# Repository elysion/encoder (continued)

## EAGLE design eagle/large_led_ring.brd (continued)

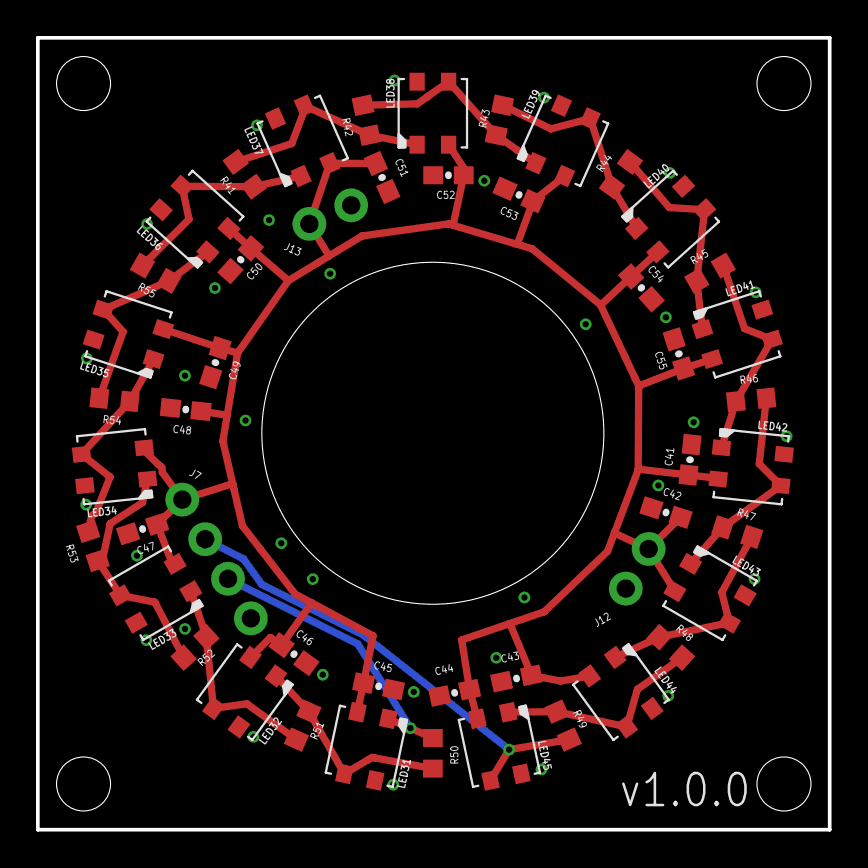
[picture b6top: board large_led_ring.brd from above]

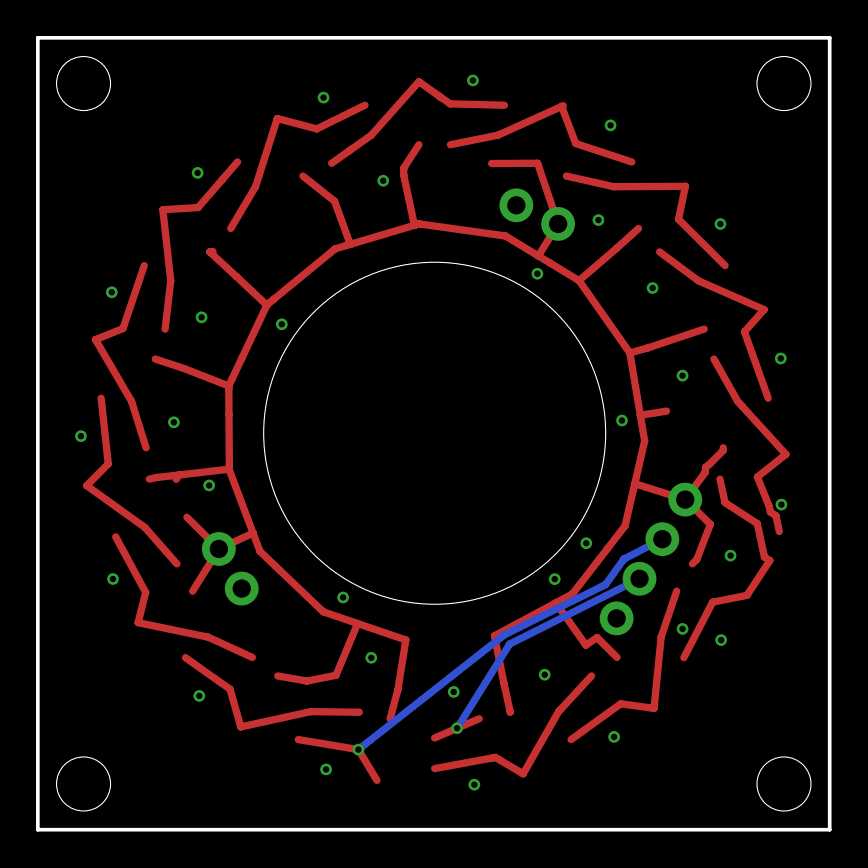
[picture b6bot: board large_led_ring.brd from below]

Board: 2 copper layers, 44.0 x 44.0 mm, 48 parts (3 on the bottom side), 18 nets.

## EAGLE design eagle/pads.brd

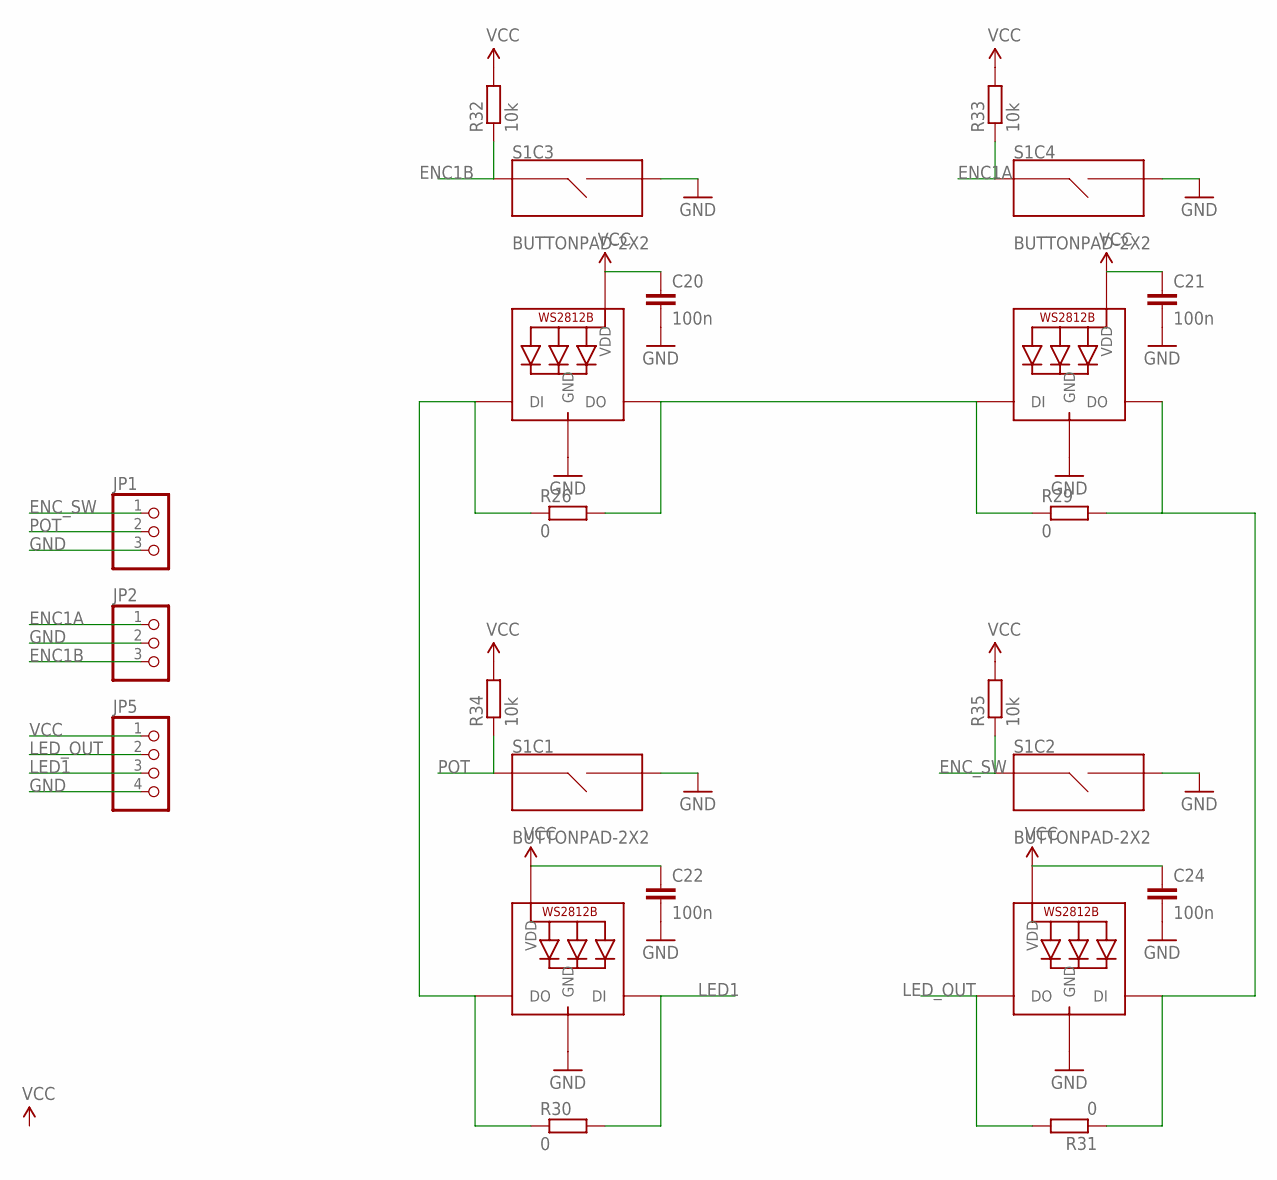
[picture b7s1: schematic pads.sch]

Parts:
C20, C21, C22, C24: 100n; 0603-CAP
JP1, JP2: PINHD-1X31X03_SMT; 1X03_SMT
JP5: PINHD-1X41X04_SMT; 1X04_SMT
LED16, LED17, LED18, LED19: WS2812B3535; LED3535
R26, R29, R30, R31: 0; R0603
R32, R33, R34, R35: 10k; R0603
S1: BUTTONPAD-2X2; BUTTONPAD-2X2-SINGLE

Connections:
ENC1A: JP2.1, R33.1, S1.SIG7 (SIG1)
ENC1B: JP2.3, R32.1, S1.SIG5 (SIG1)
ENC_SW: JP1.1, R35.1, S1.SIG3 (SIG1)
GND: C20.2, C21.2, C22.2, C24.2, JP1.3, JP2.2, JP5.4, LED16.4 (GND), LED17.4 (GND), LED18.4 (GND), LED19.4 (GND), S1.SIG2, S1.SIG4 (SIG2), S1.SIG6 (SIG2), S1.SIG8 (SIG2)
LED1: JP5.3, LED16.1 (DI), R30.2
LED_OUT: JP5.2, LED17.3 (DO), R31.2
unnamed: LED16.3 (DO), LED18.1 (DI), R26.1, R30.1
unnamed: LED17.1 (DI), LED19.3 (DO), R29.2, R31.1
unnamed: LED18.3 (DO), LED19.1 (DI), R26.2, R29.1
POT: JP1.2, R34.1, S1.SIG1
VCC: C20.1, C21.1, C22.1, C24.1, JP5.1, LED16.2 (VDD), LED17.2 (VDD), LED18.2 (VDD), LED19.2 (VDD), R32.2, R33.2, R34.2, R35.2

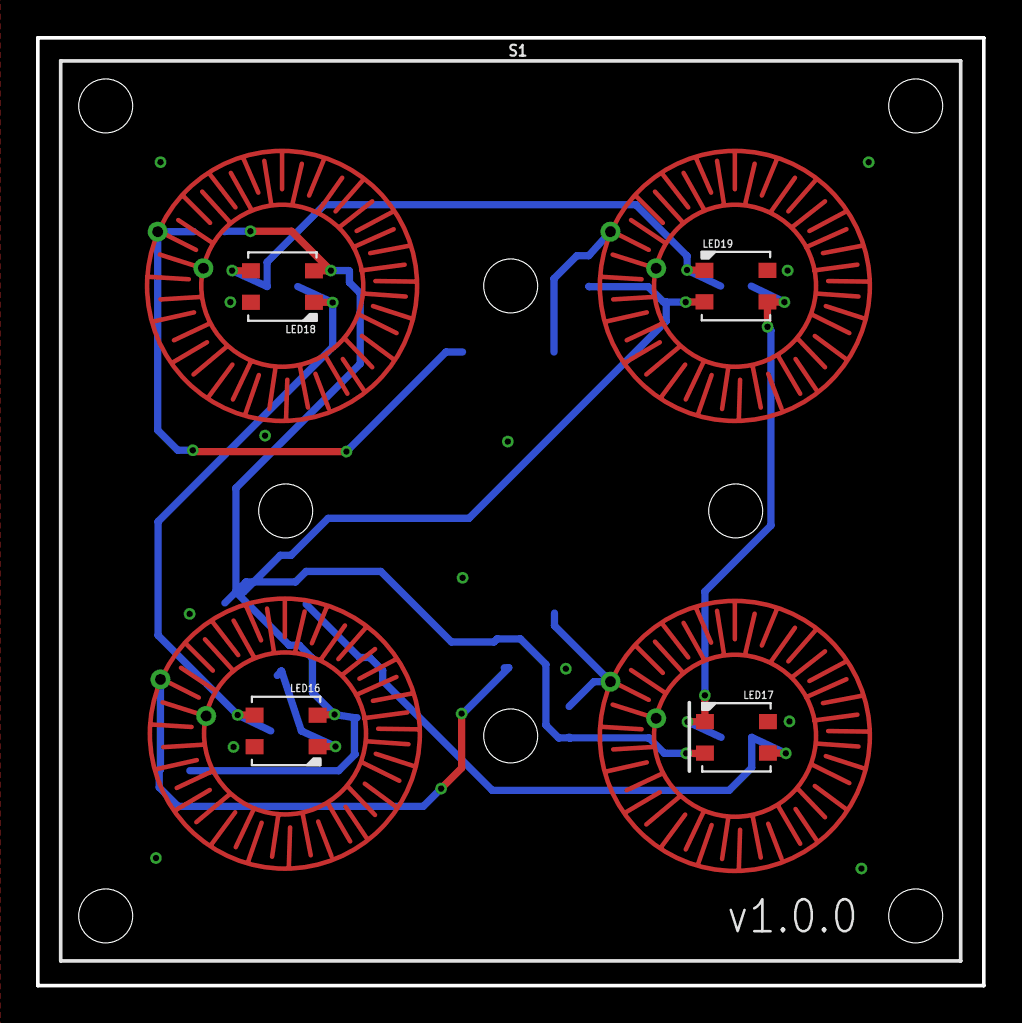
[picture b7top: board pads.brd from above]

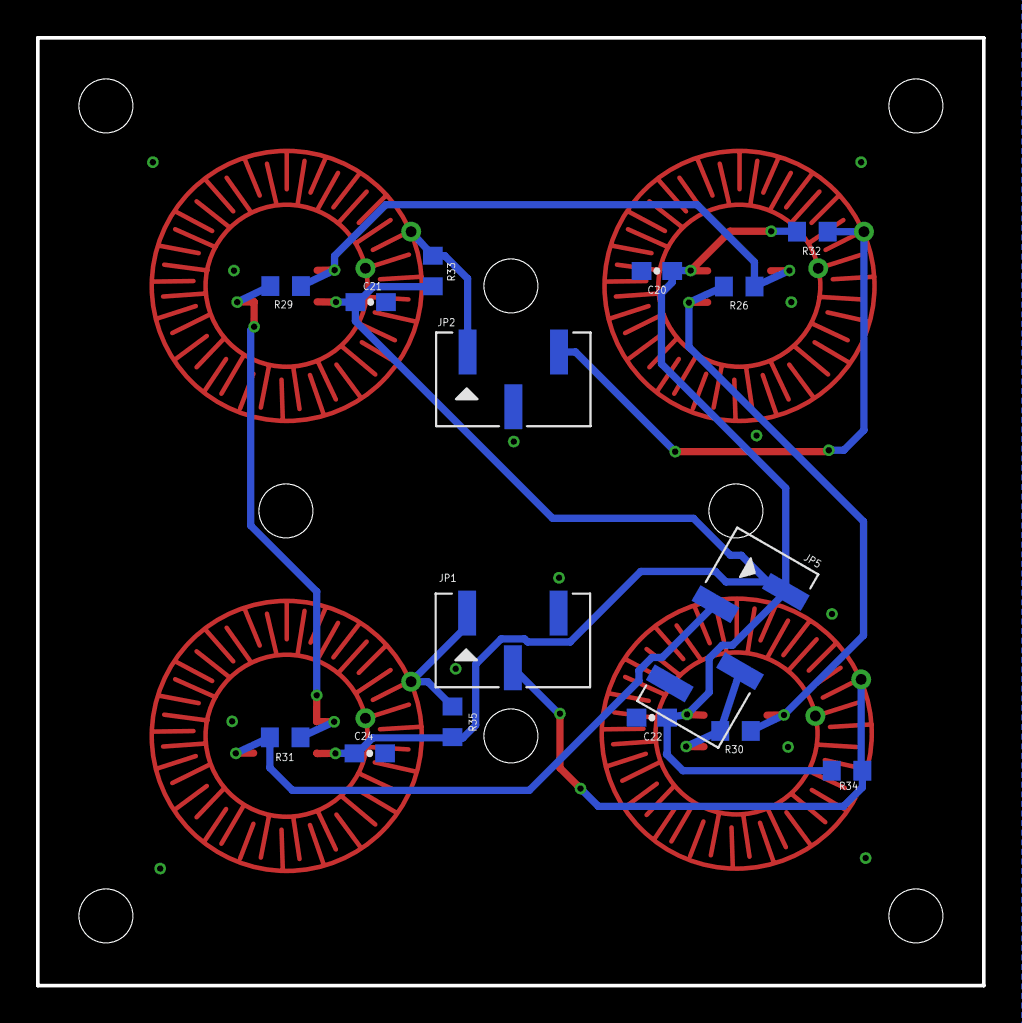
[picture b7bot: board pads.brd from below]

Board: 2 copper layers, 52.6 x 52.7 mm, 20 parts (15 on the bottom side), 11 nets.

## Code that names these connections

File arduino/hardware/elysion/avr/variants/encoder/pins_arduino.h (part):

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// ATMEL ATMEGA8 & 168 / ARDUINO
//
//                  +-\/-+
//            PC6  1|    |28  PC5 (AI 5)
//      (D 0) PD0  2|    |27  PC4 (AI 4)
//      (D 1) PD1  3|    |26  PC3 (AI 3)
//      (D 2) PD2  4|    |25  PC2 (AI 2)
// PWM+ (D 3) PD3  5|    |24  PC1 (AI 1)
//      (D 4) PD4  6|    |23  PC0 (AI 0)
//            VCC  7|    |22  GND
//            GND  8|    |21  AREF
//            PB6  9|    |20  AVCC
//            PB7 10|    |19  PB5 (D 13)
// PWM+ (D 5) PD5 11|    |18  PB4 (D 12)
// PWM+ (D 6) PD6 12|    |17  PB3 (D 11) PWM
//      (D 7) PD7 13|    |16  PB2 (D 10) PWM
//      (D 8) PB0 14|    |15  PB1 (D 9) PWM
//                  +----+
//
// (PWM+ indicates the additional PWM pins on the ATmega168.)
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
const uint8_t PROGMEM digital_pin_to_port_PGM[] = {
	NOT_A_PIN,
	PD, // PD3
	PD, // PD4
	NOT_A_PIN, // GND
	NOT_A_PIN, // VCC
	NOT_A_PIN, // GND
	NOT_A_PIN, // VCC
	PB, // PB6
	PB, // PB7
	PD, // PD5
	PD, // PD6
	PD, // PD7
	PB, // PB0
	PB, // PB1
	PB, // PB2
	PB, // PB3
	PB, // PB4
	PB, // PB5
	NOT_A_PIN, // VCC
	NOT_A_PIN, // ADC6
	NOT_A_PIN, // AREF
	NOT_A_PIN, // GND
	NOT_A_PIN, // ADC7
	PC, // PC0
	PC, // PC1
	PC, // PC2
	PC, // PC3
	PC, // PC4
	PC, // PC5
	PC, // PC6
	PD, // PD0
	PD, // PD1
	PD, // PD2
};

const uint8_t PROGMEM digital_pin_to_bit_mask_PGM[] = {
    0,
	_BV(3), // PD3
	_BV(4), // PD4
	0, // GND
	0, // VCC
	0, // GND
	0, // VCC
	_BV(6), // PB6
	_BV(7), // PB7
	_BV(5), // PD5
	_BV(6), // PD6
	_BV(7), // PD7
	_BV(0), // PB0
	_BV(1), // PB1
	_BV(2), // PB2
	_BV(3), // PB3
	_BV(4), // PB4
	_BV(5), // PB5
	0, // VCC
	0, // ADC6
	0, // AREF
	0, // GND
	0, // ADC7
	_BV(0), // PC0
	_BV(1), // PC1
	_BV(2), // PC2
	_BV(3), // PC3
	_BV(4), // PC4
	_BV(5), // PC5
	_BV(6), // PC6
	_BV(0), // PD0
	_BV(1), // PD1
	_BV(2), // PD2
};

const uint8_t PROGMEM digital_pin_to_timer_PGM[] = {
	NOT_ON_TIMER,
	TIMER2B, // PD3
	NOT_ON_TIMER, // PD4
	NOT_ON_TIMER, // GND
	NOT_ON_TIMER, // VCC
	NOT_ON_TIMER, // GND
	NOT_ON_TIMER, // VCC
	NOT_ON_TIMER, // PB6
	NOT_ON_TIMER, // PB7
	TIMER0B, // PD5
	TIMER0A, // PD6
	NOT_ON_TIMER, // PD7
	NOT_ON_TIMER, // PB0
	TIMER1A, // PB1
	TIMER1B, // PB2
	TIMER2A, // PB3
	NOT_ON_TIMER, // PB4
	NOT_ON_TIMER, // PB5
	NOT_ON_TIMER, // VCC
	NOT_ON_TIMER, // ADC6
	NOT_ON_TIMER, // AREF
	NOT_ON_TIMER, // GND
	NOT_ON_TIMER, // ADC7
	NOT_ON_TIMER, // PC0
	NOT_ON_TIMER, // PC1
	NOT_ON_TIMER, // PC2
	NOT_ON_TIMER, // PC3
	NOT_ON_TIMER, // PC4
	NOT_ON_TIMER, // PC5
	NOT_ON_TIMER, // PC6
	NOT_ON_TIMER, // PD0
	NOT_ON_TIMER, // PD1
	NOT_ON_TIMER, // PD2
};

#endif /* ARDUINO_MAIN */
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// TODO: Update for new version / create a new header / define a version macro
#if PCB_VERSION == 1
// L2 MSK1
#define ENCL2A (25)
#define ENCL2B (26)
// L1 MSK2
#define ENCL1A (2)
#define ENCL1B (32)
// M MSK2
#define ENC1A (31)
#define ENC1B (30)
// R1 MSK0
#define ENCR1A (8)
#define ENCR1B (7)
// R2 MSK1 & MSK0
#define ENCR2A (23)
#define ENCR2B (13)

// MSK2
#define SWL (1)
#define SWM (11)
#define SWR (9)
#define SWITCH_PORT (PIND)
#elif PCB_VERSION == 2 // TODO: these correspond to pins in i2c_encoder_4.*
#define ENC1A (30)
#define ENC1B (26)

// TODO: check the values below
#define ENCL1A (1)
#define ENCL1B (2)
#define ENCL2A (32)
#define ENCL2B (31)
#define ENCR1A (7)
#define ENCR1B (8)
#define ENCR2A (12)
#define ENCR2B (13)
#define SWM (23)
#define SWL (24)
#define SWR (25)
#define SWITCH_PORT (PINC)
#elif PCB_VERSION == 3
#define ENCM1A (9)
#define ENCM1B (10)
#define ENCM2A (12)
#define ENCM2B (13)
#define ENCL1A (23)
#define ENCL1B (24)
#define ENCL2A (31)
#define ENCL2B (30)
#define ENCR1A (2)
#define ENCR1B (1)
#define ENCR2A (7)
#define ENCR2B (8)
#define SWM (19)
#define SWL (22)
#define SWR (26)
#endif

#define TOUCH (11)

#if PCB_VERSION == 3
#define LEDL (25)
#define LEDM (11)
#define LEDR (32)
#else
#if PCB_VERSION == 1
#define LED1 (24)
#elif PCB_VERSION == 2
#define LED1 (9)
#endif
#define LED2 (10)
#endif

#if PCB_VERSION != 3
// TODO: On v2 SWM is connected to TOUCH -> Not an analog input
#define POTM SWM
#define POTL SWL
#define POTR SWR
#endif

#define NOT_POSSIBLE (-1)
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#endif

#if PCB_VERSION == 3 // TODO: add interrupt mask validation (i.e. != -1)
static const uint8_t SW_INTS_MASK = (1 << digitalPinToPCMSKbit(SWM));
#else
static const uint8_t SW_INTS_MASK = (1 << digitalPinToPCMSKbit(SWL)) | (1 << digitalPinToPCMSKbit(SWM)) | (1 << digitalPinToPCMSKbit(SWR));
#endif

#if PCB_VERSION == 3
static const uint8_t SW_INTS[] = {(byte) NOT_POSSIBLE, (byte) NOT_POSSIBLE, digitalPinToPCMSKbit(SWM), (byte) NOT_POSSIBLE};
#else
static const uint8_t SW_INTS[] = {(byte) NOT_POSSIBLE, digitalPinToPCMSKbit(SWL), digitalPinToPCMSKbit(SWM), digitalPinToPCMSKbit(SWR)};
#endif
/*
static const uint8_t TOUCH_INTS[] = {(byte) NOT_POSSIBLE, SWL_INT, PCINT23, SWR_INT};
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
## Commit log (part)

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2019-04-01 Add custom Arduino board
2019-04-01 Add Eagle design files
2019-04-14 Modularize WIP
2019-04-23 TEMP
2019-09-17 Add version text to boards;
    Make the text locked in order to make replacing it with e.g. sed easier
2019-09-17 TEMP: encoders working with weird delay, buttons not workin
2019-09-17 Add utility for updating board versions
2019-10-11 Move Arduino hardware files under arduino folder
2019-10-11 Make constants explicitly static
2019-10-11 Move configuration to config.h
2019-10-11 Rename SW1 to SWM and POT1 to POTM;
    Requires an updated pins_arduino.h
2019-10-11 Re-introduce encoder types;
    Was somehow removed at some point :shrug:
2019-10-12 Add Eagle temp files to ignore
2019-10-12 Toggle built-in led on boot and when sending messages
2019-10-12 Remove unnecessary comment
2019-10-12 Add feature validation into VCS;
    Somehow it was not added before.
2019-10-12 Add panelization command generator sheet
2019-10-13 Initialize PCINTs with enablePCINT
2019-10-13 Blink slave led to know it is alive and well
2019-10-13 Separate I2C and interrupt setup to functions
2019-10-13 Better indent for #define
2019-10-13 Remove warnings when compiling
2019-10-13 Comment out potentiometer code from v3
2019-10-13 Add warnings to prevent accidential freezes on ISRs
2019-10-13 FIX: update ANY_BOARD_HAS_FEATURE to include M1 and M2 for v3;
    Why does this not fail when using the old version with the newer PCB?
    BOARD_FEATURES_M should not be defined!
2019-10-13 Add parenthesis to fix switch state reading logic
2019-10-20 WIP multiple button support
2019-10-20 Add FFC connector interface versions to boards;
    It would be nice to keep the versions such that minor updates are
    backward compatible i.e. older encoder boards work with newer connector
    boards if the IF version difference is only a minor one.
2019-10-20 Add pogoprog pads on both sides of board
2019-10-20 Update switch voltage divider and connect encoder touch to it
2019-10-20 Make room for v-score on the edges by rotating connectors 45degs
2019-10-20 Board version 4 WIP;
    * Added solder pads to FFC connectors
    * Fixed naming of connectors (previously M was on the right and labels
    were wrong
    * Flipped builtin led (D1) around to make it safer to use with encoders
2019-10-22 Fix connector board issues for manufacuring;
    The minimum trace width and clearance allowed on a 1.6mm thick pcb is
    6mils. For some reason 4mils was used when designing the board (maybe
    JLCPCB design rules?).
    Also some of the texts were on the wrong layers / places and would not
    be printed on the board / would be printed on top of components / other
    texts.
2019-10-22 Fix encoder only board issues for manufacturing;
    The board was a couple of mils too wide to get 3x3 boards on a panel.
    Thus the components were moved a bit to the left and traces squeezed to
    fit in a smaller space.
    Also there were some duplicate texts in the jumper "legends" below the
    encoder and those texts were removed.
    The hole on the right top corner was moved to a symmetrical position
2019-10-26 Fix ISRs for PCB version 1
2019-10-26 Fix manufacturing issues in connector board;
    * The design rules used previously were wrong. The minimun trace widht,
    clearance and drill size were too small. The correct values are as
    follows:
    * Minimum via drill: 0.3mm
    * Minimum trace width: 6mils
    * Minimum clearance: 6mils
2019-10-26 Fix button state getter for PCB versions < 3
2019-10-26 Only include onboard led blinking in PCB version 3 firmware
2019-10-26 Indent precompiler ifs
2019-10-26 Prevent USART_DEBUG issues using feature validation instead of #ifndef;
    To be decided: Should the compile fail if there are incompatible
    features enabled, or should the incompatible features be disabled? In
    this case should the encoder on M / L2 be disabled if USART_DEBUG is
    enabled or should the compilation fail instead?
2019-10-28 Do not repeat USART_DEBUG_ENABLED in feature validation
2019-10-28 Implement port state debugging feature (enabled with PORT_STATE_DEBUG)
2019-10-28 Implement sketch for testing encoders and connector
2019-10-28 Use Board enum values for button state reading to remove magic numbers
2019-10-28 Implement TICK_BOARD marco for handling encoder reading in ISRs;
    This removes duplication that caused a lot of bugs.
2019-10-28 Remove configurations from slave.ino (should be in config.h)
2019-10-28 Implement relative encoder support
2019-10-28 Remove PCB version 3 button debug code
2019-10-28 Update previousSwitchStates only if states have changed
2019-10-28 Enable feature validation by including it in config.h;
    SHARED_INVALID_COMBINATION assertions do not currently work and thus
    were disabled.
2019-10-30 Implement button matrix feature
2020-01-06 Grid and version update for connector_board.brd
2020-01-06 Fix USART_DEBUG_ENABLED flag tests
2020-02-19 Fix encoder interrupt mapping;
    For some reason these seemed to be all wrong. The current assignments
    are based on the latest PCB design and the ATMEGA168 pinout.
2020-02-19 Make it possible to use buttons also on L2 and R2;
    The previous design only allowed for one of the boards in the chain
    to have a button (basically the one closest to the connector board).
    The latest PCB design with it's voltage divider setup enables the use
    of two buttons. However if both buttons are pressed at the same time,
    there might not be an interrupt generated on the second press and also
    reading the value from the line might not work correctly.
2020-02-19 Prevent configuring L2 as encoder when USART debug is enabled on PCBv3;
    The L2 encoder uses RX and TX pins and thus the encoder will not work
    properly when using the serial port and also there will be errors in the
    serial communication when turning the encoder.
2020-02-19 Wait before boot when unable to receive address;
    Without the wait, the debug print would not be sent before the boot.
2020-02-19 Add wait before I2C initialization to prevent race condition with master;
    Before this change the slave would only get the address from the master
    if the slave was configured so that it needed to setup all boards as
    encoder boards. When trying to initialize the board configured to have
    only a button matrix, it seemed to fail to get the address and caused
    the whole bus to freeze. The idea in this fix is to give the master some
    time to boot before starting to request addresses from it.
2020-02-19 Add debug prints for position changes
2020-02-19 Update the FFC adapter to use bottom contact connectors;
    The previous design had the pin orders to match those in the connector
    board. When using a forward direction cable (contacts on the same side
    on both ends) and a top contact connector on both ends, the pin order
    would get mirrored. Because the forward direction cable and the top
    contact connectors are (supposedly?) the norm, it's probably better to
    just reverse the pins on the adapter in order to be able to use the same
2020-03-29 Separate application specific code and "libary" code;
    In order to be able to use the slave code as a library for different
    projects without needing to fork the whole codebase, the common setup,
    event handling, etc. logic should be separated from the application
    specific logic. This commit tries to do just that, but does not
    completely succeed. The generic setup code depends on the application
    specific setup code (i.e. config.h) and thus that file has to be
2020-03-29 Add defines to shared.h to prevent multiple inclusions
2020-03-29 Implement button support for PCBv3;
    Unlike the previous PCB versions, in the v3 there are no interrupts
    available for the buttons and thus they need to be polled.
2020-03-29 Remove dead code
2020-03-29 Update pin definitions for PCB v3;
    For some reason these were all wrong :shrug:. Might be that there was
    some version that actually used these mappings... although it might as
    well be that no versions did.
2020-03-29 Move Serial.end call from slave.cpp to slave.ino;
    This was moved when moving code from the application specific code to
    the "library code". The application should control wether or not Serial
    is used and thus it makes more sense to have the Serial.end call in the
    Slave.ino file.
2020-03-29 Add the ability to limit encoder values
2020-03-29 Make sure master and slave share the message format sent via i2c
2020-03-29 Change slave address type;
    The I2C message (SlaveToMasterMessage) treats address as a single byte
    value. The address is also stored in the EEPROM as a single byte. Thus
    it makes little sense to have the address as integer in the code.
2020-03-29 Prevent button control number collisions;
    If there are multiple buttons on the same board (i.e. pads or a button
    matrix) there needs to be something to differentiate the button events
    from different buttons. This commit adds board * 20 to the control/input
    value in order to enable max 20 buttons on each board (which is way more
    than currently possible).
2020-03-29 Reverse board L2 and L1 order;
    This is to make the LED handling easier, i.e. to be able to count the
    starting led correctly on fills, because the first board in the chain
    will be the first in the Board enum and other lists.
2020-03-29 Use #ifdef instead of #if defined()
2020-03-29 Do not initiate USART if USART_DEBUG_ENABLED is not set;
    Calling begin might mess up the interrupts attached to L2. Not sure
    tough.
2020-03-29 Do not call LED functions if none of the boards have LEDs;
    This should have been done already in previous commits where the LED
    stuff was #ifdef'd.
2020-03-29 Extract requestAddress from setup code to a separate function
2020-03-29 Update LED counts
2020-03-29 Fix issues based on compiler warnings
2020-03-29 Set all encoder directions to CW;
    To use the LED rings, the encoders had to be soldered on the opposite
    side of the PCB. It would be better to have the encoder and the
    connectors on different sides in future versions of the PCBs.
2020-03-29 Update headers to use de facto #define naming
2020-03-29 Update board configurations
2020-03-29 Use LED_COUNT constants to initiate the LEDs
2020-03-29 Add support for CCW encoders
2020-03-29 Control LEDs on individual boards rather than always use R1;
    R1 was used because previously there were no LED rings on other boards.
2020-03-29 Make range check function inline
2020-03-29 Fix color type;
    Using uint16_t instead of uint32_t caused the colors to be wrong (red
    color (20,0,0) was displayed as green.
2020-03-29 Initialize LED rings to position 0 on setup
2020-03-29 Update button PCINT initializations for PCB v3;
    There seems to be 2 PCBs with v3. One with PCINT for SWR (lastest) and
    one with PCINT for SWM.
2020-03-29 Share master address and address length between master and slave
2020-03-29 Fix slave I2C initialization;
    This error caused a reboot loop on devices that had their EEPROM erased.
2020-03-29 Initialize NeoPixel array
2020-03-29 Remove unnecessary rgbw color function;
    The LEDs used in the project are rgb and thus this function is not
    needed (at least for this project).
2020-03-29 Fix indent
2020-03-30 Update colors in LED rings;
    It probably makes more sense helping to differentiate the channels in
    the same group rather than differentiating the different groups.
2020-03-30 Fix compilation issue;
    Direction needs to be cast to a integer in order to use it in
    calculation.
2020-03-30 Implement a loop / wrap around function to absolute encoders
2020-03-30 Use #pragma once instead of custom #defines
2020-03-30 Add board versions to boards.txt
2020-03-30 Add MIDI master example
2020-03-30 Do not include debug led initialization if led is not used
2020-03-30 Remove debug prints if serial debug is not enabled to save space;
    Single call to Serial.print will increase the hex size by 2k.
2020-03-30 Separate potentiometer handling from encoder handling
2020-03-30 Reorder config.h;
    Move the feature selection to the top and the more specific
    configurations after that.
2020-03-30 Remove debugging code
